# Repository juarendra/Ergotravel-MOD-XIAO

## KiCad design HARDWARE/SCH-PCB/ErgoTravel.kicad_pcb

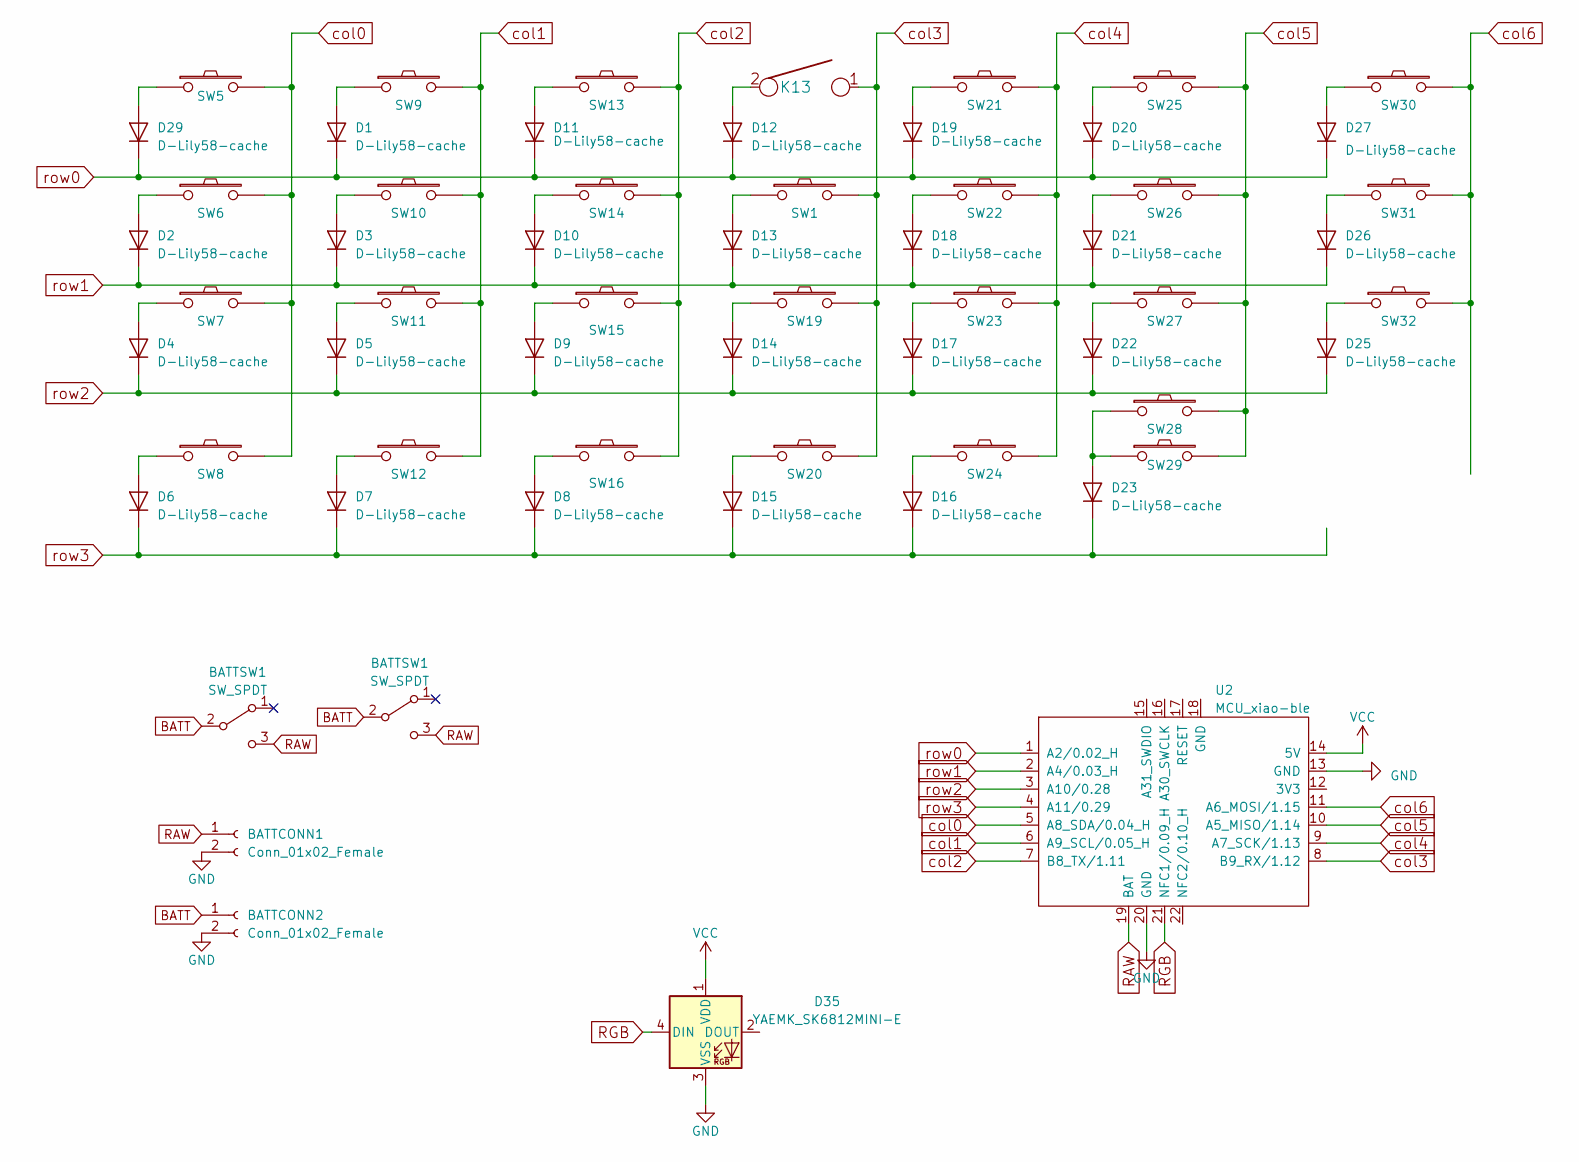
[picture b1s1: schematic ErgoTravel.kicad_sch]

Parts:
BATTCONN1, BATTCONN2: Conn_01x02_Female; Connector_JST-1x02-2.00mm
BATTSW1: SW_SPDT; Switch_SPDT-PCM12
D1, D2, D3, D4, D5, D6, D7, D8, D9, D10, D11, D12, D13, D14, D15, D16, D17, D18, D19, D20, D21, D22, D23, D25, D26, D27, D29: D-Lily58-cache; Diode_SOD123
D35: YAEMK_SK6812MINI-E; SK6812_mini_e_flipable
K13: KEYSW; SW_MX_reversible
SW1, SW5, SW6, SW7, SW8, SW9, SW10, SW11, SW12, SW13, SW14, SW15, SW16, SW19, SW20, SW21, SW22, SW23, SW24, SW25, SW26, SW27, SW28, SW29, SW30, SW31, SW32: SW_PUSH-Lily58-cache; CherryMX_Hotswap
U2: MCU_xiao-ble; MCU_xiao-ble-tht

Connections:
BATT: BATTCONN2.1, BATTSW1.2 (B); also elsewhere on the board
GND: BATTCONN1.2, BATTCONN2.2, U2.13 (GND), U2.20 (GND); also elsewhere on the board
unnamed: D1.2 (A), SW9.1
unnamed: D2.2 (A), SW6.1
unnamed: D3.2 (A), SW10.1
unnamed: D4.2 (A), SW7.1
unnamed: D5.2 (A), SW11.1
unnamed: D6.2 (A), SW8.1
unnamed: D7.2 (A), SW12.1
unnamed: D8.2 (A), SW16.1
unnamed: D9.2 (A), SW15.1
unnamed: D10.2 (A), SW14.1
unnamed: D11.2 (A), SW13.1
unnamed: D12.2 (A), K13.2
unnamed: D13.2 (A), SW1.1
unnamed: D14.2 (A), SW19.1
unnamed: D15.2 (A), SW20.1
unnamed: D16.2 (A), SW24.1
unnamed: D17.2 (A), SW23.1
unnamed: D18.2 (A), SW22.1
unnamed: D19.2 (A), SW21.1
unnamed: D20.2 (A), SW25.1
unnamed: D21.2 (A), SW26.1
unnamed: D22.2 (A), SW27.1
unnamed: D23.2 (A), SW28.1, SW29.1
unnamed: D25.2 (A), SW32.1
unnamed: D26.2 (A), SW31.1
unnamed: D27.2 (A), SW30.1
unnamed: D29.2 (A), SW5.1
RAW: BATTCONN1.1, BATTSW1.3 (C), U2.19 (BAT); also elsewhere on the board
RGB: U2.21 (NFC1/0.09_H); also elsewhere on the board
VCC: U2.14 (5V); also elsewhere on the board
col0: SW5.2, SW6.2, SW7.2, SW8.2, U2.5 (A8_SDA/0.04_H)
col1: SW9.2, SW10.2, SW11.2, SW12.2, U2.6 (A9_SCL/0.05_H)
col2: SW13.2, SW14.2, SW15.2, SW16.2, U2.7 (B8_TX/1.11)
col3: K13.1, SW1.2, SW19.2, SW20.2, U2.8 (B9_RX/1.12)
col4: SW21.2, SW22.2, SW23.2, SW24.2, U2.9 (A7_SCK/1.13)
col5: SW25.2, SW26.2, SW27.2, SW28.2, SW29.2, U2.10 (A5_MISO/1.14)
col6: SW30.2, SW31.2, SW32.2, U2.11 (A6_MOSI/1.15)
row0: D1.1 (K), D11.1 (K), D12.1 (K), D19.1 (K), D20.1 (K), D27.1 (K), D29.1 (K), U2.1 (A2/0.02_H)
row1: D2.1 (K), D3.1 (K), D10.1 (K), D13.1 (K), D18.1 (K), D21.1 (K), D26.1 (K), U2.2 (A4/0.03_H)
row2: D4.1 (K), D5.1 (K), D9.1 (K), D14.1 (K), D17.1 (K), D22.1 (K), D25.1 (K), U2.3 (A10/0.28)
row3: D6.1 (K), D7.1 (K), D8.1 (K), D15.1 (K), D16.1 (K), D23.1 (K), U2.4 (A11/0.29)

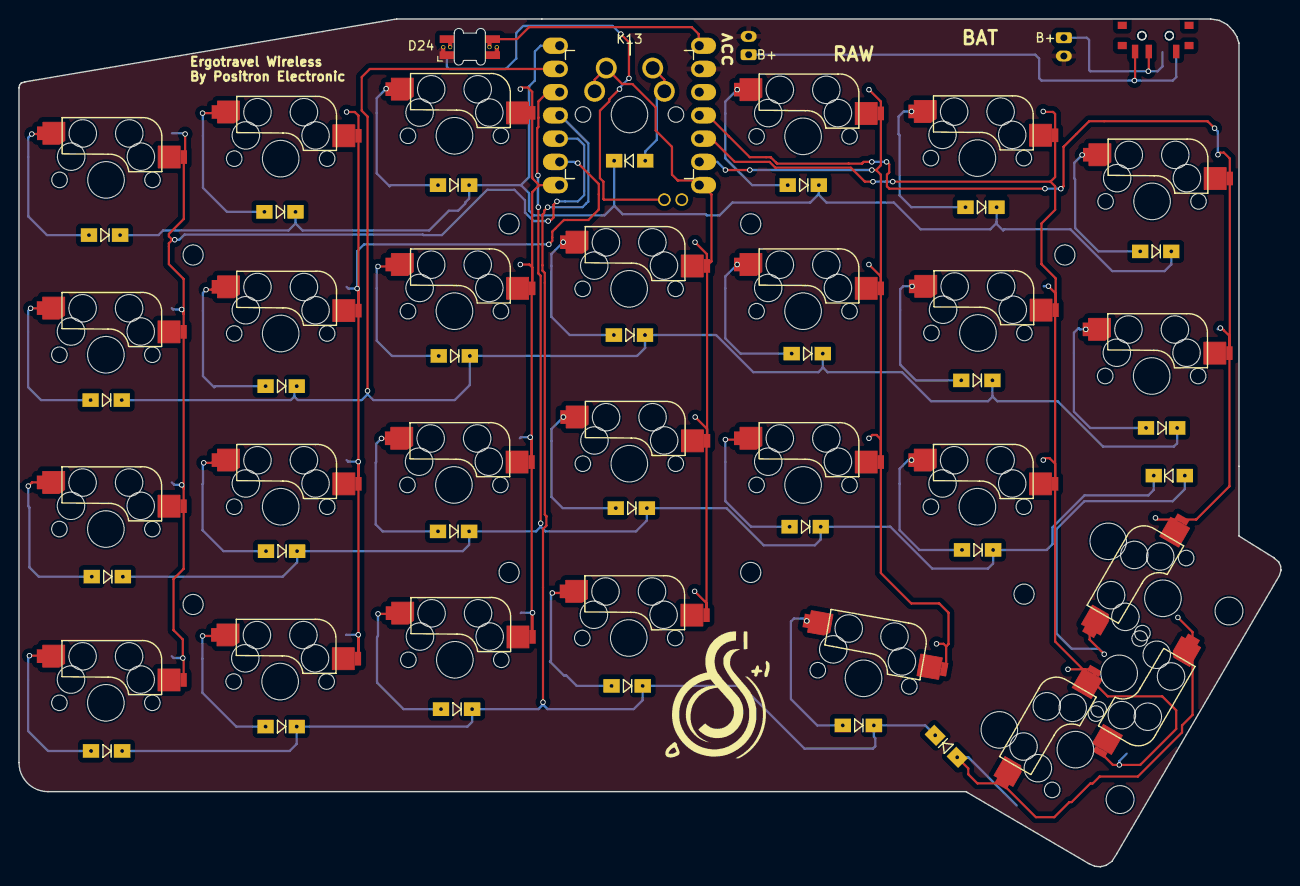
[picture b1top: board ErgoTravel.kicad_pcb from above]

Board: 2 copper layers, 137.9 x 92.7 mm, 70 parts (1 on the bottom side), 43 nets.

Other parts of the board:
BATTSW2: SW_SPDT; Switch_SPDT-PCM12
D24: YAEMK_SK6812MINI-E; SK6812_mini_e_flipable
H1: MountingHole; Stabilizer_MX_2u
J5, J6, J7, J8, J9, J10, J11, J12: Conn_01x01; MountingHole_2.2mm_M2_DIN965

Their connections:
BATT: BATTSW2.2 (B); also elsewhere on the board
GND: D24.3 (VSS); also elsewhere on the board
RAW: BATTSW2.3 (C); also elsewhere on the board
RGB: D24.4 (DIN); also elsewhere on the board
VCC: D24.1 (VDD); also elsewhere on the board

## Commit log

2024-07-08 FEAT: add Hardware Dimentions
2024-07-08 FEAT: add Hardware schematic
2024-07-08 FEAT: add image doc
2024-07-09 DOC: add readme
2024-07-09 FEAT: add 3d model and case
